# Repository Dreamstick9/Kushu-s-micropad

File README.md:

# Kushu-s-micropad

## Inspiration
I wanted to create a "Megapad" that wasn't just keys—I needed control. I designed a custom macropad featuring **6 keys, 2 rotary encoders, and an OLED screen** so I could manage volume, scroll through pages, and see my layer status all at once. It's the ultimate desk companion for productivity (and fidgeting).

## Challenges        

**Fusion 360 was a nightmare at first.** I'd never used it before, and just getting the sketches to lock in or the mouse controls to cooperate felt like a puzzle. The hardest technical hurdle was the mechanical integration specifically the USB-C port alignment and the internal clearance for the tall encoder pins.

There was a moment near the end where I almost skipped the final "Crash Test" because I was just done. I didn't think I had it in me to import the PCB into the case and align the joints. But I pushed through, learned how to use "Section Analysis" to X-Ray the case, and verified that the top plate sat flush on the shoulders without hitting the standoffs. Seeing that perfect cross section view in the end was the only thing that convinced me it would actually work.

## Specifications

### BOM:
* **1x** XIAO RP2040
* **6x** MX-Style Mechanical Switches
* **2x** EC11 Rotary Encoders (with push button)
* **1x** 0.91" OLED Display (I2C)
* **6x** 1N4148 Diodes
* **4x** M3x16 Bolts
* **4x** M3 Heatset Inserts
* **1x** 3D Printed Case & Plate

### Others:
* **Firmware:** KMK Firmware (CircuitPython)
* **Files:**
    * `Megapad_Full_Assembly.step` (CAD)
    * `gerbers.zip` (PCB Fabrication)

# Schematic

# PCB

# Case

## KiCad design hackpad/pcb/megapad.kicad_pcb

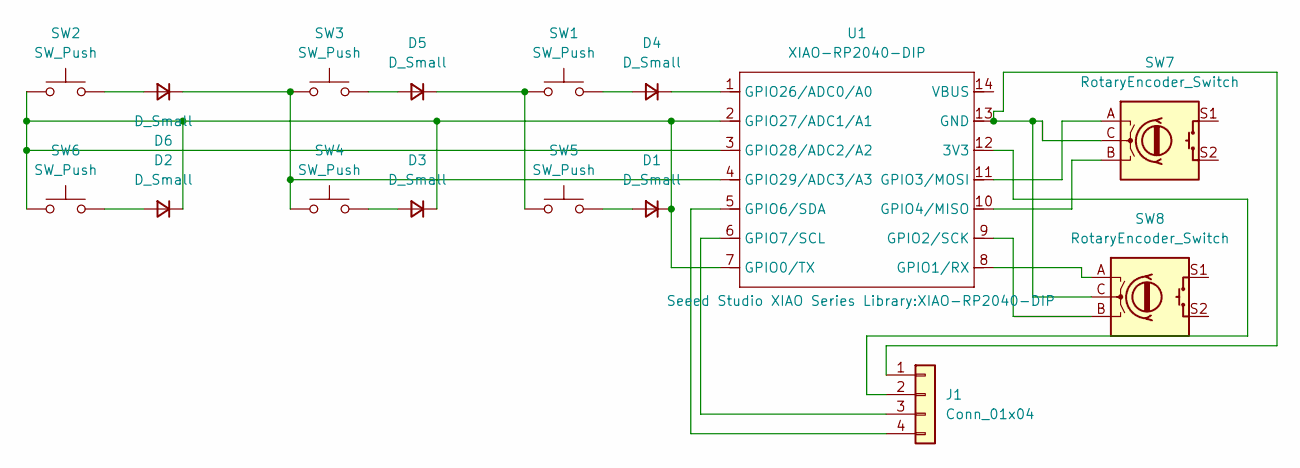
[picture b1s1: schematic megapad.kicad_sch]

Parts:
D1, D2, D3, D4, D5, D6: D_Small; D_DO-35_SOD27_P7.62mm_Horizontal
J1: Conn_01x04; PinHeader_1x04_P2.54mm_Vertical
SW1, SW2, SW3, SW4, SW5, SW6: SW_Push; SW_Cherry_MX_1.00u_PCB
SW7, SW8: RotaryEncoder_Switch; RotaryEncoder_Alps_EC11E-Switch_Vertical_H20mm
U1: XIAO-RP2040-DIP

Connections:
unnamed: D1.2 (A), SW5.2
unnamed: D1.1 (K), D2.1 (K), D3.1 (K), SW2.1, SW6.1, U1.2 (GPIO27/ADC1/A1), U1.3 (GPIO28/ADC2/A2), U1.7 (GPIO0/TX)
unnamed: D2.2 (A), SW6.2
unnamed: D3.2 (A), SW4.2
unnamed: D4.2 (A), SW1.2
unnamed: D4.1 (K), U1.1 (GPIO26/ADC0/A0)
unnamed: D5.2 (A), SW3.2
unnamed: D5.1 (K), SW1.1, SW5.1
unnamed: D6.2 (A), SW2.2
unnamed: D6.1 (K), SW3.1, SW4.1, U1.4 (GPIO29/ADC3/A3)
unnamed: J1.1, SW7.C, SW8.C, U1.13 (GND)
unnamed: J1.2, U1.12 (3V3)
unnamed: J1.3, U1.6 (GPIO7/SCL)
unnamed: J1.4, U1.5 (GPIO6/SDA)
unnamed: SW8.A, U1.8 (GPIO1/RX)
unnamed: SW8.B, U1.9 (GPIO2/SCK)
unnamed: SW7.A, U1.11 (GPIO3/MOSI)
unnamed: SW7.B, U1.10 (GPIO4/MISO)

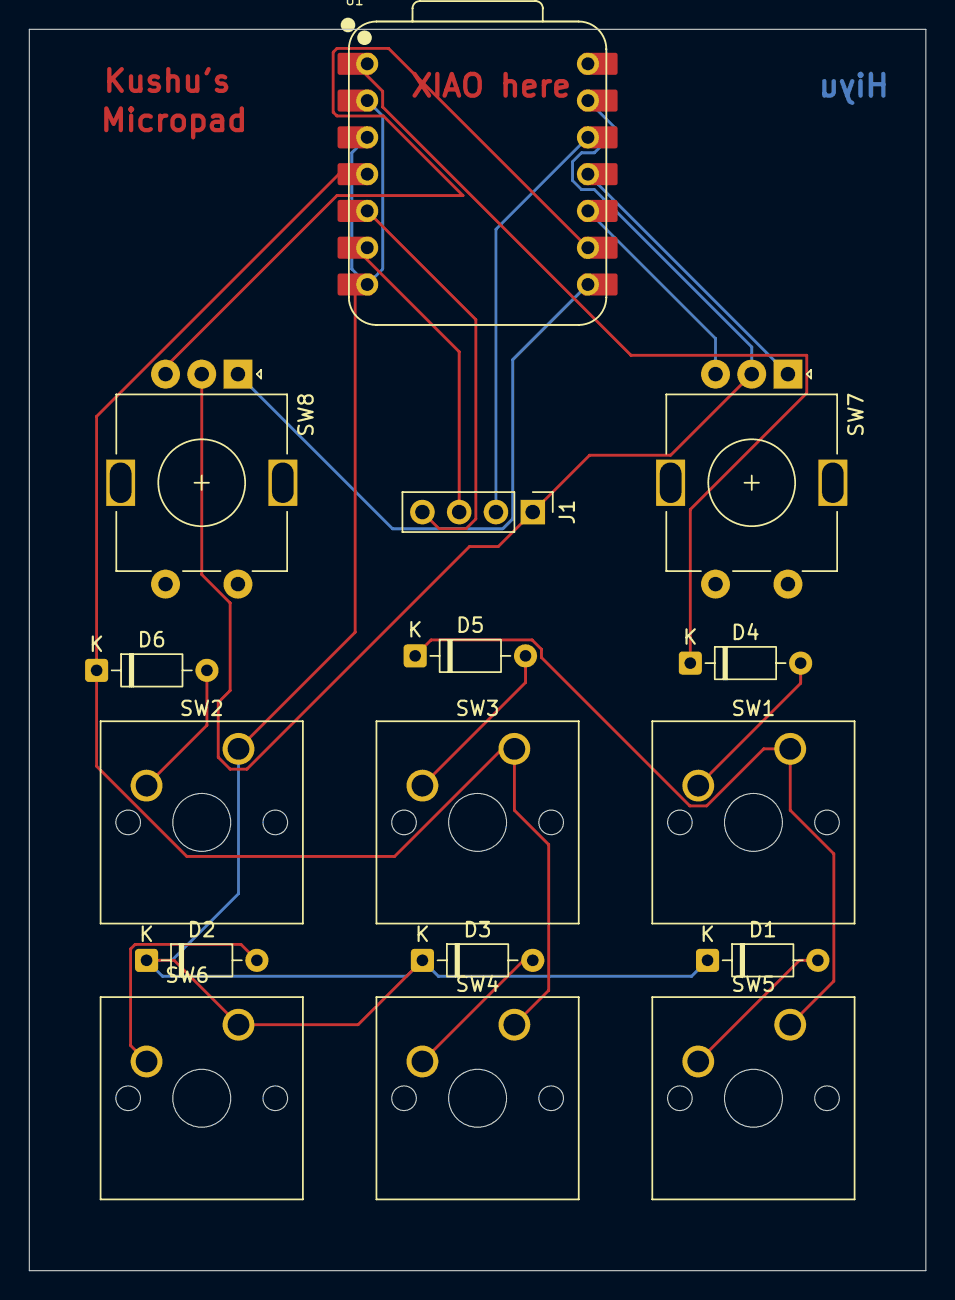
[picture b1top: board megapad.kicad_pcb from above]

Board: 2 copper layers, 61.9 x 85.7 mm, 16 parts (0 on the bottom side), 18 nets.

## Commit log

2025-12-27 Enhance README with project details and images
    Added detailed project description, specifications, and images.
2025-12-28 remove old files
2025-12-28 renamed main.py
2026-01-26 changed the step file with some edits on the name on the bottom part of the case
